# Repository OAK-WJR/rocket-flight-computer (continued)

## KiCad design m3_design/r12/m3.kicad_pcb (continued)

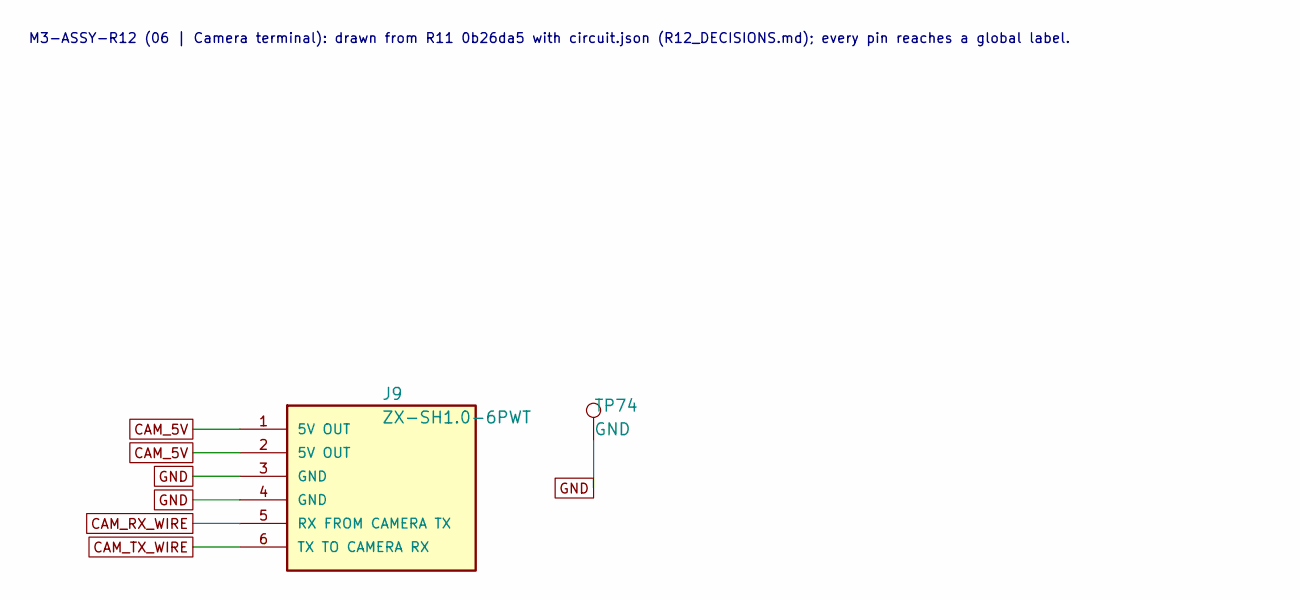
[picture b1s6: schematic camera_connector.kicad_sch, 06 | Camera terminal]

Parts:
J9: ZX-SH1.0-6PWT; M3_SHC_6P; Manufacturer Part ZX-SH1.0-6PWT; LCSC C7430448
TP74: GND; M3_TestPad_1.5

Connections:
CAM_5V: J9.1 (5V OUT), J9.2 (5V OUT); also elsewhere on the board
CAM_RX_WIRE: J9.5 (RX FROM CAMERA TX); also elsewhere on the board
CAM_TX_WIRE: J9.6 (TX TO CAMERA RX); also elsewhere on the board
GND: J9.3 (GND), J9.4 (GND), TP74.1; also elsewhere on the board

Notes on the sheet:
M3-ASSY-R12 (06 | Camera terminal): drawn from R11 0b26da5 with circuit.json (R12_DECISIONS.md); every pin reaches a global label.

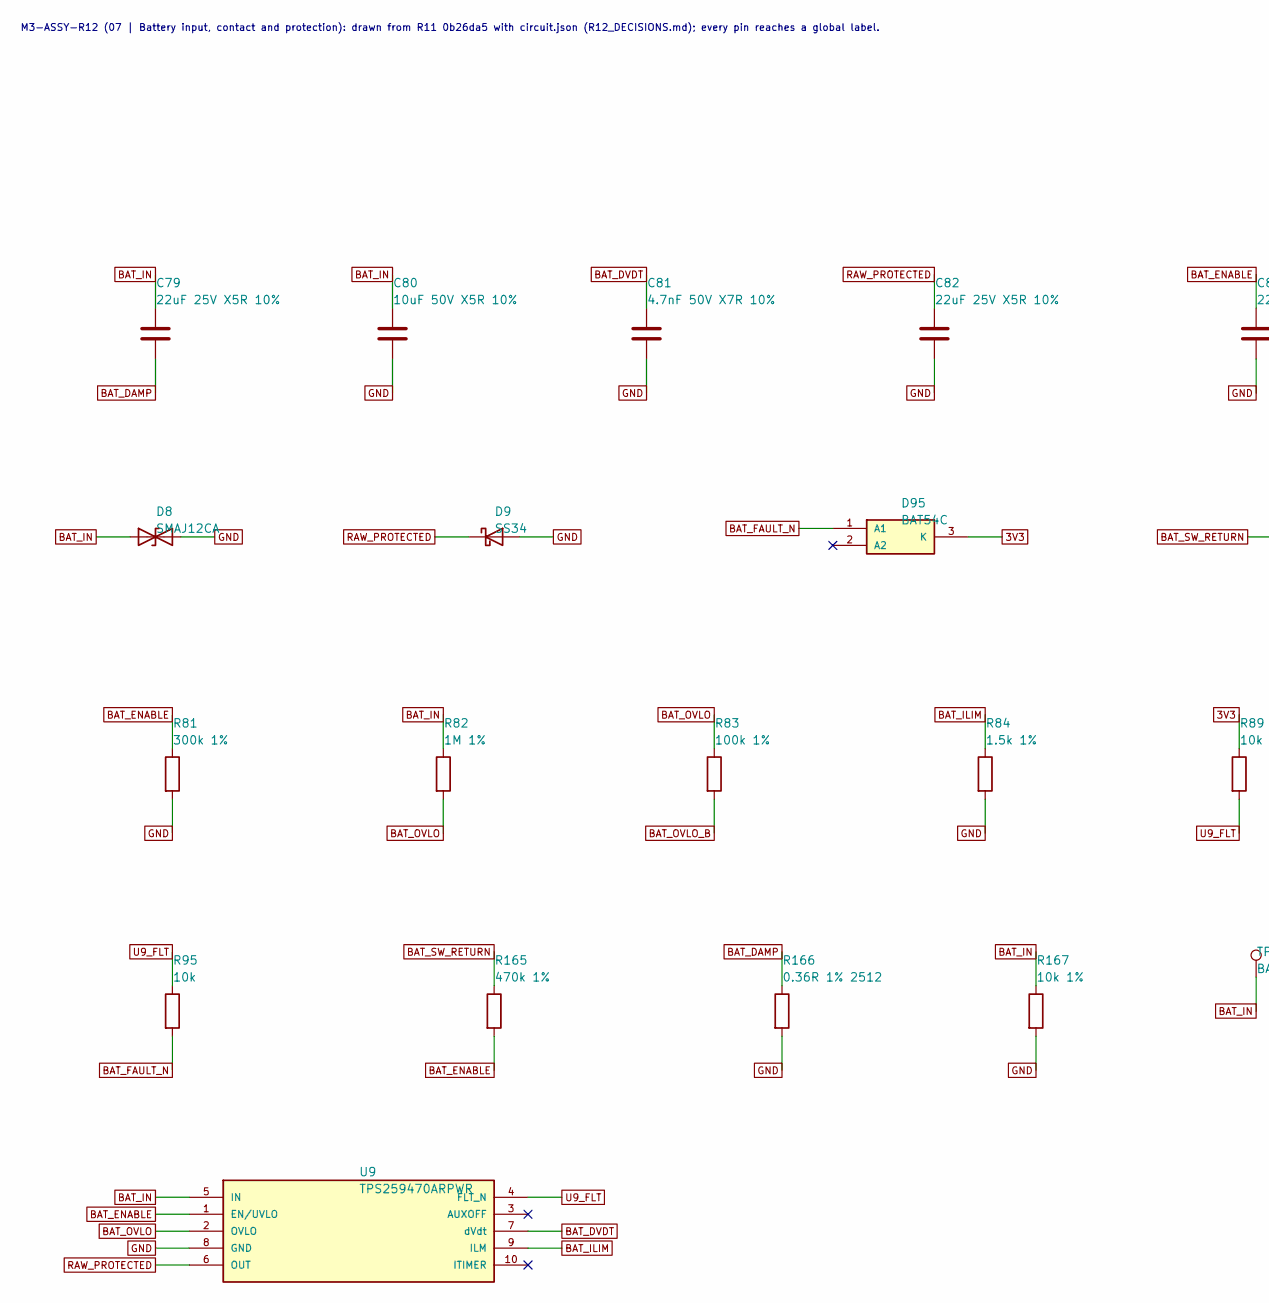
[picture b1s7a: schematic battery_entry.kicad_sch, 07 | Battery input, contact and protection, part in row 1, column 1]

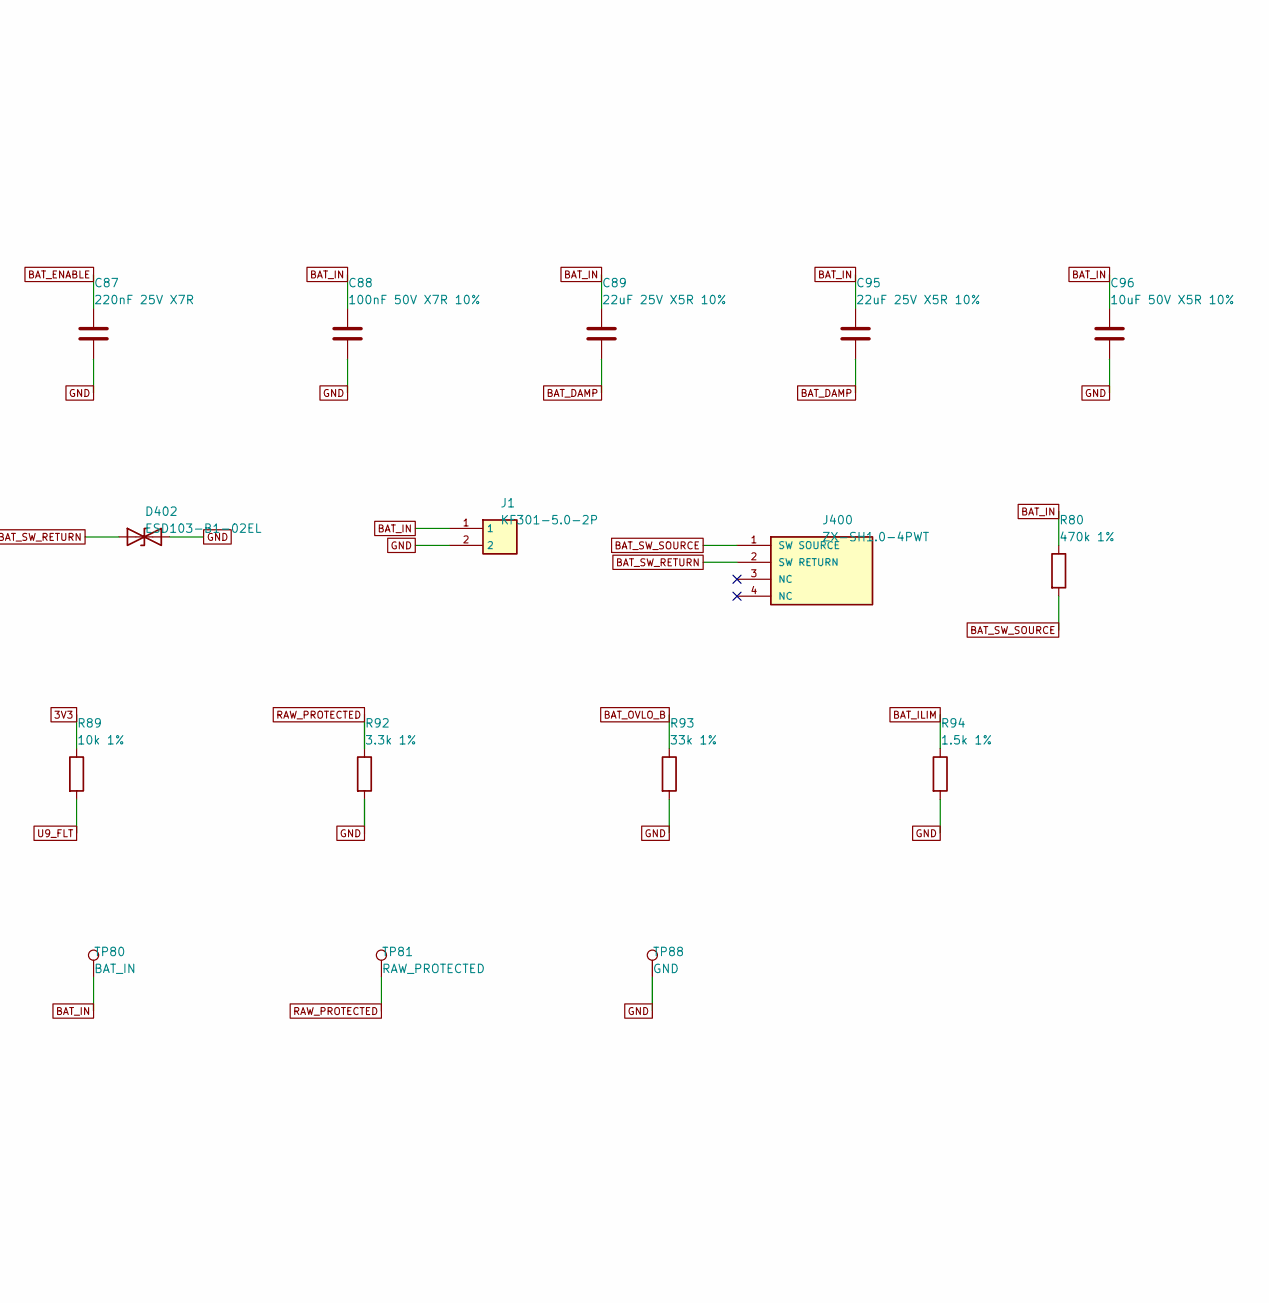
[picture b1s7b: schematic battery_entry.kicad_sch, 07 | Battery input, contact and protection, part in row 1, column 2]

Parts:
C79, C82, C89, C95: 22uF 25V X5R 10%; C_1206_3216Metric; Manufacturer Part CL31A226KAHNNNE; LCSC C12891
C80, C96: 10uF 50V X5R 10%; C_1206_3216Metric; Manufacturer Part CL31A106KBHNNNE; LCSC C13585
C81: 4.7nF 50V X7R 10%; C0402; Manufacturer Part 0402B472K500NT; LCSC C1538
C87: 220nF 25V X7R; C0603; Manufacturer Part CL10B224KA8NNNC; LCSC C21120
C88: 100nF 50V X7R 10%; C0402; Manufacturer Part CL05B104KB54PNC; LCSC C307331
D8: SMAJ12CA; D_SMA; Manufacturer Part SMAJ12CA; LCSC C19077532
D9: SS34; D_SMA; Manufacturer Part SS34; LCSC C8678
D95: BAT54C; SOT-23-3_L2.9-W1.3-P1.90-LS2.4-BR; Manufacturer Part BAT54C,215; LCSC C37704
D402: ESD103-B1-02EL; M3_TSLP_2_20; Manufacturer Part ESD103-B1-02EL E6327; LCSC C535146
J1: KF301-5.0-2P; M3_KF301_5P0_2P_BU; Manufacturer Part KF301-5.0-2P; LCSC C474881
J400: ZX-SH1.0-4PWT; M3_SHC_4P; Manufacturer Part ZX-SH1.0-4PWT; LCSC C7430446
R80, R165: 470k 1%; R_0603_1608Metric; Manufacturer Part 0603WAF4703T5E; LCSC C23178
R81: 300k 1%; R_0603_1608Metric; Manufacturer Part 0603WAF3003T5E; LCSC C23024
R82: 1M 1%; R0402; Manufacturer Part 0402WGF1004TCE; LCSC C26083
R83: 100k 1%; R0402; Manufacturer Part 0402WGF1003TCE; LCSC C25741
R84, R94: 1.5k 1%; R0402; Manufacturer Part 0402WGF1501TCE; LCSC C25867
R89, R167: 10k 1%; R0402; Manufacturer Part 0402WGF1002TCE; LCSC C25744
R92: 3.3k 1%; R_0603_1608Metric; Manufacturer Part 0603WAF3301T5E; LCSC C22978
R93: 33k 1%; R0402; Manufacturer Part 0402WGF3302TCE; LCSC C25779
R95: 10k; R0402; Manufacturer Part 0402WGF1002TCE; LCSC C25744
R166: 0.36R 1% 2512; M3_R2512_UR; Manufacturer Part 25121WF360LT4E; LCSC C168925
TP80: BAT_IN; M3_TestPad_1.5
TP81: RAW_PROTECTED; M3_TestPad_1.5
TP88: GND; M3_TestPad_1.5
U9: TPS259470ARPWR; M3_TPS25947_RPW; Manufacturer Part TPS259470ARPWR; LCSC C3662799

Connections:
3V3: D95.3 (K), R89.1; also elsewhere on the board
BAT_DAMP: C79.2, C89.2, C95.2, R166.1
BAT_DVDT: C81.1, U9.7 (dVdt)
BAT_ENABLE: C87.1, R81.1, R165.2, U9.1 (EN/UVLO)
BAT_FAULT_N: D95.1 (A1), R95.2; also elsewhere on the board
BAT_ILIM: R84.1, R94.1, U9.9 (ILM)
BAT_IN: C79.1, C80.1, C88.1, C89.1, C95.1, C96.1, D8.1 (A1), J1.1, R80.1, R82.1, R167.1, TP80.1, U9.5 (IN); also elsewhere on the board
BAT_OVLO: R82.2, R83.1, U9.2 (OVLO)
BAT_OVLO_B: R83.2, R93.1
BAT_SW_RETURN: D402.1 (A1), J400.2 (SW RETURN), R165.1
BAT_SW_SOURCE: J400.1 (SW SOURCE), R80.2
GND: C80.2, C81.2, C82.2, C87.2, C88.2, C96.2, D8.2 (A2), D9.2 (A), D402.2 (A2), J1.2, R81.2, R84.2, R92.2, R93.2, R94.2, R166.2, R167.2, TP88.1, U9.8 (GND); also elsewhere on the board
RAW_PROTECTED: C82.1, D9.1 (K), R92.1, TP81.1, U9.6 (OUT); also elsewhere on the board
U9_FLT: R89.2, R95.1, U9.4 (FLT_N)

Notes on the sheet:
M3-ASSY-R12 (07 | Battery input, contact and protection): drawn from R11 0b26da5 with circuit.json (R12_DECISIONS.md); every pin reaches a global label.

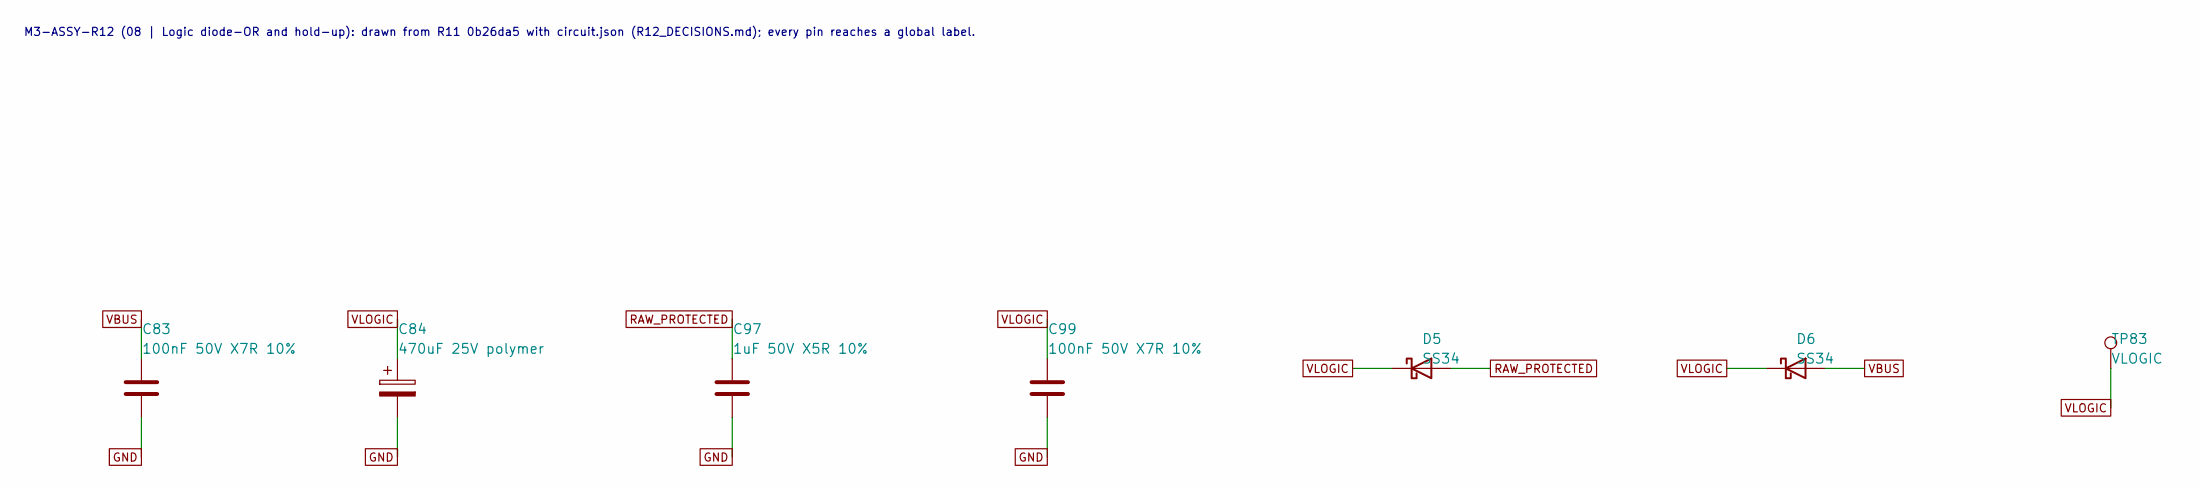
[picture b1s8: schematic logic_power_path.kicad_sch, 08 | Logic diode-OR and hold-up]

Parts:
C83, C99: 100nF 50V X7R 10%; C0402; Manufacturer Part CL05B104KB54PNC; LCSC C307331
C84: 470uF 25V polymer; M3_CAP_D8_SMD; Manufacturer Part HV1E477M0810PZ; LCSC C5246546
C97: 1uF 50V X5R 10%; C0603; Manufacturer Part CL10A105KB8NNNC; LCSC C15849
D5, D6: SS34; D_SMA; Manufacturer Part SS34; LCSC C8678
TP83: VLOGIC; M3_TestPad_1.5

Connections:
GND: C83.2, C84.2, C97.2, C99.2; also elsewhere on the board
RAW_PROTECTED: C97.1, D5.2 (A); also elsewhere on the board
VBUS: C83.1, D6.2 (A); also elsewhere on the board
VLOGIC: C84.1, C99.1, D5.1 (K), D6.1 (K), TP83.1; also elsewhere on the board

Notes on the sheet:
M3-ASSY-R12 (08 | Logic diode-OR and hold-up): drawn from R11 0b26da5 with circuit.json (R12_DECISIONS.md); every pin reaches a global label.

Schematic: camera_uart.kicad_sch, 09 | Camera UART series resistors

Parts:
R100, R101: 1k 1%; R0402; Manufacturer Part 0402WGF1001TCE; LCSC C11702

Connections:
CAM_MCU_RX: R100.2; also elsewhere on the board
CAM_MCU_TX: R101.1; also elsewhere on the board
CAM_RX_WIRE: R100.1; also elsewhere on the board
CAM_TX_WIRE: R101.2; also elsewhere on the board

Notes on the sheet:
M3-ASSY-R12 (09 | Camera UART series resistors): drawn from R11 0b26da5 with circuit.json (R12_DECISIONS.md); every pin reaches a global label.

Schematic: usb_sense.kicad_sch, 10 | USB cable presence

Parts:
R9: 1k; R0402; Manufacturer Part 0402WGF1001TCE; LCSC C11702
R110: 1.5k 1%; R0402; Manufacturer Part 0402WGF1501TCE; LCSC C25867

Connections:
GND: R110.2; also elsewhere on the board
VBUS: R9.1; also elsewhere on the board
VBUS_SENSE: R9.2, R110.1; also elsewhere on the board

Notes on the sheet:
M3-ASSY-R12 (10 | USB cable presence): drawn from R11 0b26da5 with circuit.json (R12_DECISIONS.md); every pin reaches a global label.

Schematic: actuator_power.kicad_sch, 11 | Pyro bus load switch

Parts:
C120: 1uF 50V X5R 10%; C0603; Manufacturer Part CL10A105KB8NNNC; LCSC C15849
C123: 10nF 50V X7R 10%; C0402; Manufacturer Part CL05B103KB5NNNC; LCSC C15195
Q120, Q121: AO3401A; SOT-23-3_L2.9-W1.3-P1.90-LS2.4-BR; Manufacturer Part AO3401A; LCSC C15127
Q122: AO3400A; SOT-23-3_L2.9-W1.3-P1.90-LS2.4-BR; Manufacturer Part AO3400A; LCSC C20917
R118, R121: 10k; R0402; Manufacturer Part 0402WGF1002TCE; LCSC C25744
R119, R120: 100k; R0402; Manufacturer Part 0402WGF1003TCE; LCSC C25741
R122: 1k; R0402; Manufacturer Part 0402WGF1001TCE; LCSC C11702
R123: 2k; R0402; Manufacturer Part 0402WGF2001TCE; LCSC C4109
TP120: RAW_ACT; M3_TestPad_1.5

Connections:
ACT_DRV: Q122.3 (D), R121.2
ACT_EN: C123.1, Q122.1 (G), R118.1, R122.2, R123.1
ACT_EN_MCU: R122.1; also elsewhere on the board
ACT_FET_S: C120.1, Q120.2 (S), Q121.2 (S), R119.2, R120.1
ACT_GATE: C120.2, Q120.1 (G), Q121.1 (G), R119.1, R120.2, R121.1
BAT_IN: Q120.3 (D); also elsewhere on the board
GND: C123.2, Q122.2 (S), R118.2, R123.2; also elsewhere on the board
RAW_ACT: Q121.3 (D), TP120.1; also elsewhere on the board

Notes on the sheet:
M3-ASSY-R12 (11 | Pyro bus load switch): drawn from R11 0b26da5 with circuit.json (R12_DECISIONS.md); every pin reaches a global label.

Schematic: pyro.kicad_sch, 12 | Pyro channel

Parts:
C126: 220nF 25V X7R; C0603; Manufacturer Part CL10B224KA8NNNC; LCSC C21120
C127, C129: 10nF 50V X7R 10%; C0402; Manufacturer Part CL05B103KB5NNNC; LCSC C15195
C128: 100nF 50V X7R 10%; C0402; Manufacturer Part CL05B104KB54PNC; LCSC C307331
D120: BAT54C; SOT-23-3_L2.9-W1.3-P1.90-LS2.4-BR; Manufacturer Part BAT54C,215; LCSC C37704
J121: DB125-3.5-2P-BK-S; M3_DB125_2P_BK; Manufacturer Part DB125-3.5-2P-BK-S; LCSC C52993880
Q124: AO3400A; SOT-23-3_L2.9-W1.3-P1.90-LS2.4-BR; Manufacturer Part AO3400A; LCSC C20917
R126: 220R; R0402; Manufacturer Part 0402WGF2200TCE; LCSC C25091
R127: 1k; R0402; Manufacturer Part 0402WGF1001TCE; LCSC C11702
R128: 10k; R0402; Manufacturer Part 0402WGF1002TCE; LCSC C25744
R129, R131, R132, R136, R173, R175: 5.1k; R0402; Manufacturer Part 0402WGF5101TCE; LCSC C25905
R130, R133, R178, R180: 2k; R0402; Manufacturer Part 0402WGF2001TCE; LCSC C4109
R134: 2R 1% 2W pulse; R2512; Manufacturer Part CRM2512-FX-2R00ELF; LCSC C3013496
TP122: PYRO1_GATE; M3_TestPad_1.5

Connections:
3V3: R136.1; also elsewhere on the board
ARM1_SENSE: C129.1, R133.1, R175.2, R180.1; also elsewhere on the board
ARM1_SENSE_MID: R132.2, R175.1
GND: C126.2, C127.2, C128.2, C129.2, Q124.2 (S), R127.2, R128.2, R130.2, R133.2, R178.2, R180.2; also elsewhere on the board
PYRO1_COLD: D120.3 (K), R131.2
PYRO1_COLD_PU: D120.1 (A1), R136.2
PYRO1_CONT: C127.1, R129.2, R130.1, R178.1; also elsewhere on the board
PYRO1_CONT_MID: R129.1, R173.2
PYRO1_GATE: C126.1, Q124.1 (G), R126.2, R128.1, TP122.1
PYRO1_GATE_N: R126.1, R127.1; also elsewhere on the board
PYRO1_IGN: J121.2, R134.1
PYRO1_OUT: C128.1, J121.1, Q124.3 (D), R131.1, R173.1
RAW_ACT: R132.1, R134.2; also elsewhere on the board

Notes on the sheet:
M3-ASSY-R12 (12 | Pyro channel): drawn from R11 0b26da5 with circuit.json (R12_DECISIONS.md); every pin reaches a global label.

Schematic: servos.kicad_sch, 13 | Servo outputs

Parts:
D121: SRV05-4; SOT-23-6_L2.9-W1.6-P0.95-LS2.8-BL; Manufacturer Part SRV05-4-P-T7; LCSC C85364
J122: ZX-SH1.0-6PWT; M3_SHC_6P; Manufacturer Part ZX-SH1.0-6PWT; LCSC C7430448
R150, R151, R152, R153: 1k 0603; R_0603_1608Metric; Manufacturer Part 0603WAF1001T5E; LCSC C21190
R154, R155, R156, R157: 10k; R0402; Manufacturer Part 0402WGF1002TCE; LCSC C25744

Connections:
3V3: D121.5 (VCC); also elsewhere on the board
GND: D121.2 (GND), J122.5 (GND), R154.2, R155.2, R156.2, R157.2; also elsewhere on the board
SERVO1_MCU: D121.1 (IO1), R150.1, R154.1; also elsewhere on the board
SERVO1_OUT: J122.1 (SERVO1), R150.2
SERVO2_MCU: D121.3 (IO2), R151.1, R155.1; also elsewhere on the board
SERVO2_OUT: J122.2 (SERVO2), R151.2
SERVO3_MCU: D121.4 (IO3), R152.1, R156.1; also elsewhere on the board
SERVO3_OUT: J122.3 (SERVO3), R152.2
SERVO4_MCU: D121.6 (IO4), R153.1, R157.1; also elsewhere on the board
SERVO4_OUT: J122.4 (SERVO4), R153.2

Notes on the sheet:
M3-ASSY-R12 (13 | Servo outputs): drawn from R11 0b26da5 with circuit.json (R12_DECISIONS.md); every pin reaches a global label.

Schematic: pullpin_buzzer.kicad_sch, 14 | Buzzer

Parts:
D123: 1N5819WS; SOD-323_L1.8-W1.3-LS2.5-RD; Manufacturer Part 1N5819WS; LCSC C191023
LS120: QMB-09B-03; M3_BUZ_TH_D9_P4; Manufacturer Part QMB-09B-03; LCSC C96256
Q123: AO3400A; SOT-23-3_L2.9-W1.3-P1.90-LS2.4-BR; Manufacturer Part AO3400A; LCSC C20917
R162: 1k; R0402; Manufacturer Part 0402WGF1001TCE; LCSC C11702
R163: 10k; R0402; Manufacturer Part 0402WGF1002TCE; LCSC C25744

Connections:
3V3: D123.1 (K), LS120.1 (+); also elsewhere on the board
BUZZ_DRV: R162.1; also elsewhere on the board
BUZZ_G: Q123.1 (G), R162.2, R163.1
BUZZ_OUT: D123.2 (A), LS120.2 (-), Q123.3 (D)
GND: Q123.2 (S), R163.2; also elsewhere on the board

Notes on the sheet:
M3-ASSY-R12 (14 | Buzzer): drawn from R11 0b26da5 with circuit.json (R12_DECISIONS.md); every pin reaches a global label.

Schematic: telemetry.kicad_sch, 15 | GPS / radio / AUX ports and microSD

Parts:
C460: 100nF 50V X7R 10%; C0402; Manufacturer Part CL05B104KB54PNC; LCSC C307331
C461: 22uF 25V X5R 10%; C_1206_3216Metric; Manufacturer Part CL31A226KAHNNNE; LCSC C12891
J410: ZX-SH1.0-6PWT; M3_SHC_6P; Manufacturer Part ZX-SH1.0-6PWT; LCSC C7430448
J420, J440: ZX-SH1.0-4PWT; M3_SHC_4P; Manufacturer Part ZX-SH1.0-4PWT; LCSC C7430446
J430: 104031-0811; M3_MICROSD_MOLEX_104031; Manufacturer Part 1040310811; LCSC C585350
R440, R441, R450, R451, R470, R471: 1k 1%; R0402; Manufacturer Part 0402WGF1001TCE; LCSC C11702
R460, R461, R462, R463, R464: 10k 1%; R0402; Manufacturer Part 0402WGF1002TCE; LCSC C25744

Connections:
3V3: C460.1, C461.1, J430.4 (VDD), R460.2, R461.2, R462.2, R463.2, R464.2; also elsewhere on the board
AUX_RX_MCU: R470.2; also elsewhere on the board
AUX_RX_WIRE: J440.4 (RXI), R470.1
AUX_TX_MCU: R471.1; also elsewhere on the board
AUX_TX_WIRE: J440.3 (TXO), R471.2
GND: C460.2, C461.2, J410.1 (GND), J420.1 (GND), J430.6 (VSS), J430.9 (G2), J430.10 (G1), J430.13 (G4), J430.14 (G3), J440.1 (GND); also elsewhere on the board
GPS_RX_MCU: R440.2; also elsewhere on the board
GPS_RX_WIRE: J410.4 (RXI), R440.1
GPS_TX_MCU: R441.1; also elsewhere on the board
GPS_TX_WIRE: J410.3 (TXO), R441.2
PORT_4V8: J410.2 (4V8), J420.2 (4V8), J440.2 (4V8); also elsewhere on the board
RADIO_RX_MCU: R450.2; also elsewhere on the board
RADIO_RX_WIRE: J420.4 (RXI), R450.1
RADIO_TX_MCU: R451.1; also elsewhere on the board
RADIO_TX_WIRE: J420.3 (TXO), R451.2
SD_CS: J430.2 (CD_DAT3_CS), R460.1; also elsewhere on the board
SD_DAT1: J430.8 (DAT1), R463.1
SD_DAT2: J430.1 (DAT2), R464.1
SD_MISO: J430.7 (DAT0_DO), R462.1; also elsewhere on the board
SD_MOSI: J430.3 (CMD_DI), R461.1; also elsewhere on the board
SD_SCK: J430.5 (CLK); also elsewhere on the board

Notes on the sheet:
M3-ASSY-R12 (15 | GPS / radio / AUX ports and microSD): drawn from R11 0b26da5 with circuit.json (R12_DECISIONS.md); every pin reaches a global label.

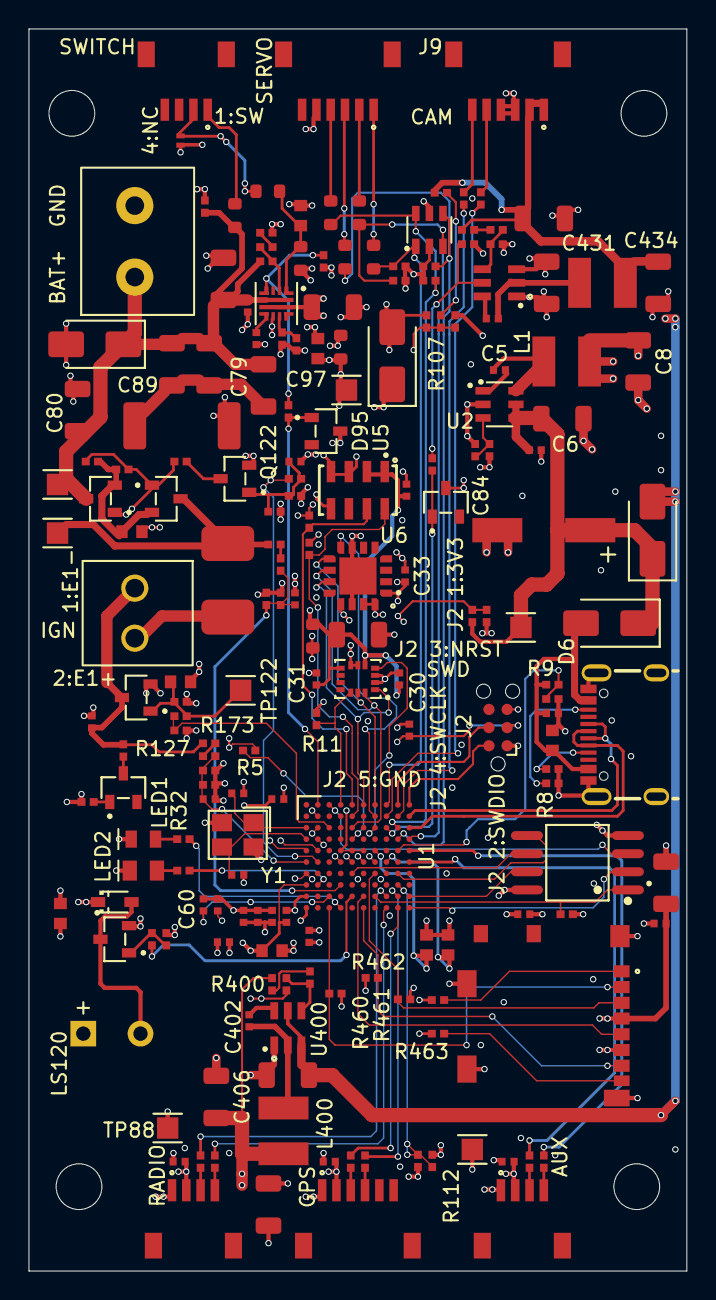
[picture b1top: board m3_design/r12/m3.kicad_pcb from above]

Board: 4 copper layers, 46.0 x 86.8 mm, 193 parts (0 on the bottom side), 116 nets.

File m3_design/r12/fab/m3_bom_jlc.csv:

Comment,Designator,Footprint,LCSC Part #,Manufacturer Part,Qty,Assembly
100nF 50V X7R 10%,"C5,C13,C14,C15,C16,C17,C18,C21,C24,C29,C30,C31,C32,C33,C83,C88,C99,C128,C402,C410,C420,C432,C444,C460",C0402,C307331,CL05B104KB54PNC,24,SMT
22uF 25V X5R 10%,"C6,C8,C10,C79,C82,C89,C95,C400,C406,C407,C431,C433,C434,C461",C_1206_3216Metric,C12891,CL31A226KAHNNNE,14,SMT
2.2uF 16V X5R 10%,"C19,C20",C0603,C23630,CL10A225KO8NNNC,2,SMT
1uF 50V X5R 10%,"C22,C97,C120",C0603,C15849,CL10A105KB8NNNC,3,SMT
4.7uF 16V X5R 10%,"C23,C28",C0603,C19666,CL10A475KO8NNNC,2,SMT
15pF 50V C0G 5%,"C25,C26",C0402,C1548,0402CG150J500NT,2,SMT
10nF 50V X7R 10%,"C60,C94,C123,C127,C129",C0402,C15195,CL05B103KB5NNNC,5,SMT
10uF 50V X5R 10%,"C80,C96",C_1206_3216Metric,C13585,CL31A106KBHNNNE,2,SMT
4.7nF 50V X7R 10%,C81,C0402,C1538,0402B472K500NT,1,SMT
470uF 25V polymer,C84,M3_CAP_D8_SMD,C5246546,HV1E477M0810PZ,1,SMT
220nF 25V X7R,"C87,C126",C0603,C21120,CL10B224KA8NNNC,2,SMT
SS34,"D5,D6,D9",D_SMA,C8678,SS34,3,SMT
SMAJ12CA,D8,D_SMA,C19077532,SMAJ12CA,1,SMT
BAT54C,"D95,D120,D436",SOT-23-3_L2.9-W1.3-P1.90-LS2.4-BR,C37704,"BAT54C,215",3,SMT
SRV05-4,D121,SOT-23-6_L2.9-W1.6-P0.95-LS2.8-BL,C85364,SRV05-4-P-T7,1,SMT
1N5819WS,D123,SOD-323_L1.8-W1.3-LS2.5-RD,C191023,1N5819WS,1,SMT
ESD103-B1-02EL,D402,M3_TSLP_2_20,C535146,ESD103-B1-02EL E6327,1,SMT
KF301-5.0-2P,J1,M3_KF301_5P0_2P_BU,C474881,KF301-5.0-2P,1,THT (JLC THT assembly)
USB-C 2.0,J3,USB-C_SMD-TYPE-C-31-M-12_1,C165948,TYPE-C-31-M-12,1,SMT
ZX-SH1.0-6PWT,"J9,J122,J410",M3_SHC_6P,C7430448,ZX-SH1.0-6PWT,3,SMT
DB125-3.5-2P-BK-S,J121,M3_DB125_2P_BK,C52993880,DB125-3.5-2P-BK-S,1,THT (JLC THT assembly)
ZX-SH1.0-4PWT,"J400,J420,J440",M3_SHC_4P,C7430446,ZX-SH1.0-4PWT,3,SMT
104031-0811,J430,M3_MICROSD_MOLEX_104031,C585350,1040310811,1,SMT
4.7uH,"L1,L400,L401",IND-SMD_L4.0-W4.0,C57269,SWPA4030S4R7MT,3,SMT
RED,LED1,M3_NCD0805R1_K1,C84256,NCD0805R1,1,SMT
YEL,LED2,M3_KT0805Y_A1,C2296,KT-0805Y,1,SMT
QMB-09B-03,LS120,M3_BUZ_TH_D9_P4,C96256,QMB-09B-03,1,THT (JLC THT assembly)
AO3401A,"Q120,Q121",SOT-23-3_L2.9-W1.3-P1.90-LS2.4-BR,C15127,AO3401A,2,SMT
AO3400A,"Q122,Q123,Q124",SOT-23-3_L2.9-W1.3-P1.90-LS2.4-BR,C20917,AO3400A,3,SMT
10k; 10k 1%,"R5,R10,R11,R89,R95,R118,R121,R128,R154,R155,R156,R157,R163,R167,R434,R435,R460,R461,R462,R463,R464",R0402,C25744,0402WGF1002TCE,21,SMT
5.1k,"R7,R8,R104,R107,R129,R131,R132,R136,R173,R175,R404,R436",R0402,C25905,0402WGF5101TCE,12,SMT
1k; 1k 1%,"R9,R100,R101,R122,R127,R162,R440,R441,R450,R451,R470,R471",R0402,C11702,0402WGF1001TCE,12,SMT
4.7k,"R12,R13",R0402,C25900,0402WGF4701TCE,2,SMT
47k 1%,"R14,R111,R400,R431",R0402,C25792,0402WGF4702TCE,4,SMT
20k 1%,R15,R0402,C25765,0402WGF2002TCE,1,SMT
220R,"R32,R33,R126",R0402,C25091,0402WGF2200TCE,3,SMT
100k 0.1%,R60,R0402,C852472,RT0402BRD07100KL,1,SMT
10k 0.1%,"R61,R401",R0402,C190095,RT0402BRD0710KL,2,SMT
470k 1%,"R80,R165",R_0603_1608Metric,C23178,0603WAF4703T5E,2,SMT
300k 1%,R81,R_0603_1608Metric,C23024,0603WAF3003T5E,1,SMT
1M 1%,R82,R0402,C26083,0402WGF1004TCE,1,SMT
100k 1%; 100k,"R83,R112,R119,R120",R0402,C25741,0402WGF1003TCE,4,SMT
1.5k 1%,"R84,R94,R110",R0402,C25867,0402WGF1501TCE,3,SMT
3.3k 1%,R92,R_0603_1608Metric,C22978,0603WAF3301T5E,1,SMT
33k 1%,R93,R0402,C25779,0402WGF3302TCE,1,SMT
2k,"R105,R106,R123,R130,R133,R178,R180",R0402,C4109,0402WGF2001TCE,7,SMT
2R 1% 2W pulse,R134,R2512,C3013496,CRM2512-FX-2R00ELF,1,SMT
1k 0603,"R150,R151,R152,R153",R_0603_1608Metric,C21190,0603WAF1001T5E,4,SMT
2.2R 1%,R164,R_0603_1608Metric,C22939,0603WAF220KT5E,1,SMT
0.36R 1% 2512,R166,M3_R2512_UR,C168925,25121WF360LT4E,1,SMT
51k 1%,R433,R0402,C25794,0402WGF5102TCE,1,SMT
STM32H743VIH6,U1,M3_TFBGA100_8x8_P0.8,C964146,STM32H743VIH6,1,SMT
LMR50410XDBVR,U2,SOT-23-6_L2.9-W1.6-P0.95-LS2.8-BL,C2841056,LMR50410XDBVR,1,SMT
W25Q128JVSIQ,U3,SOIC-8_L5.3-W5.3-P1.27-LS8.0-BL,C97521,W25Q128JVSIQ,1,SMT
LSM6DSVETR,U4,LGA-14_L3.0-W2.5-P0.50-TL,C41785564,LSM6DSVETR,1,SMT
MS5607-02BA03,U5,SENSORS-SMD_MS5611-01BA03,C97627,MS560702BA03-50,1,SMT
FXLS90322AESR2,U6,M3_FXLS_HLQFN16,C5190712,FXLS90322AESR2,1,SMT
TPS259470ARPWR,U9,M3_TPS25947_RPW,C3662799,TPS259470ARPWR,1,SMT
TPS563208DDCR,"U400,U403",M3_TSOT23_6_DDC,C468250,TPS563208DDCR,2,SMT
25MHz CL12pF,Y1,CRYSTAL-SMD_4P-L3.2-W2.5-BL,C9006,X322525MOB4SI,1,SMT

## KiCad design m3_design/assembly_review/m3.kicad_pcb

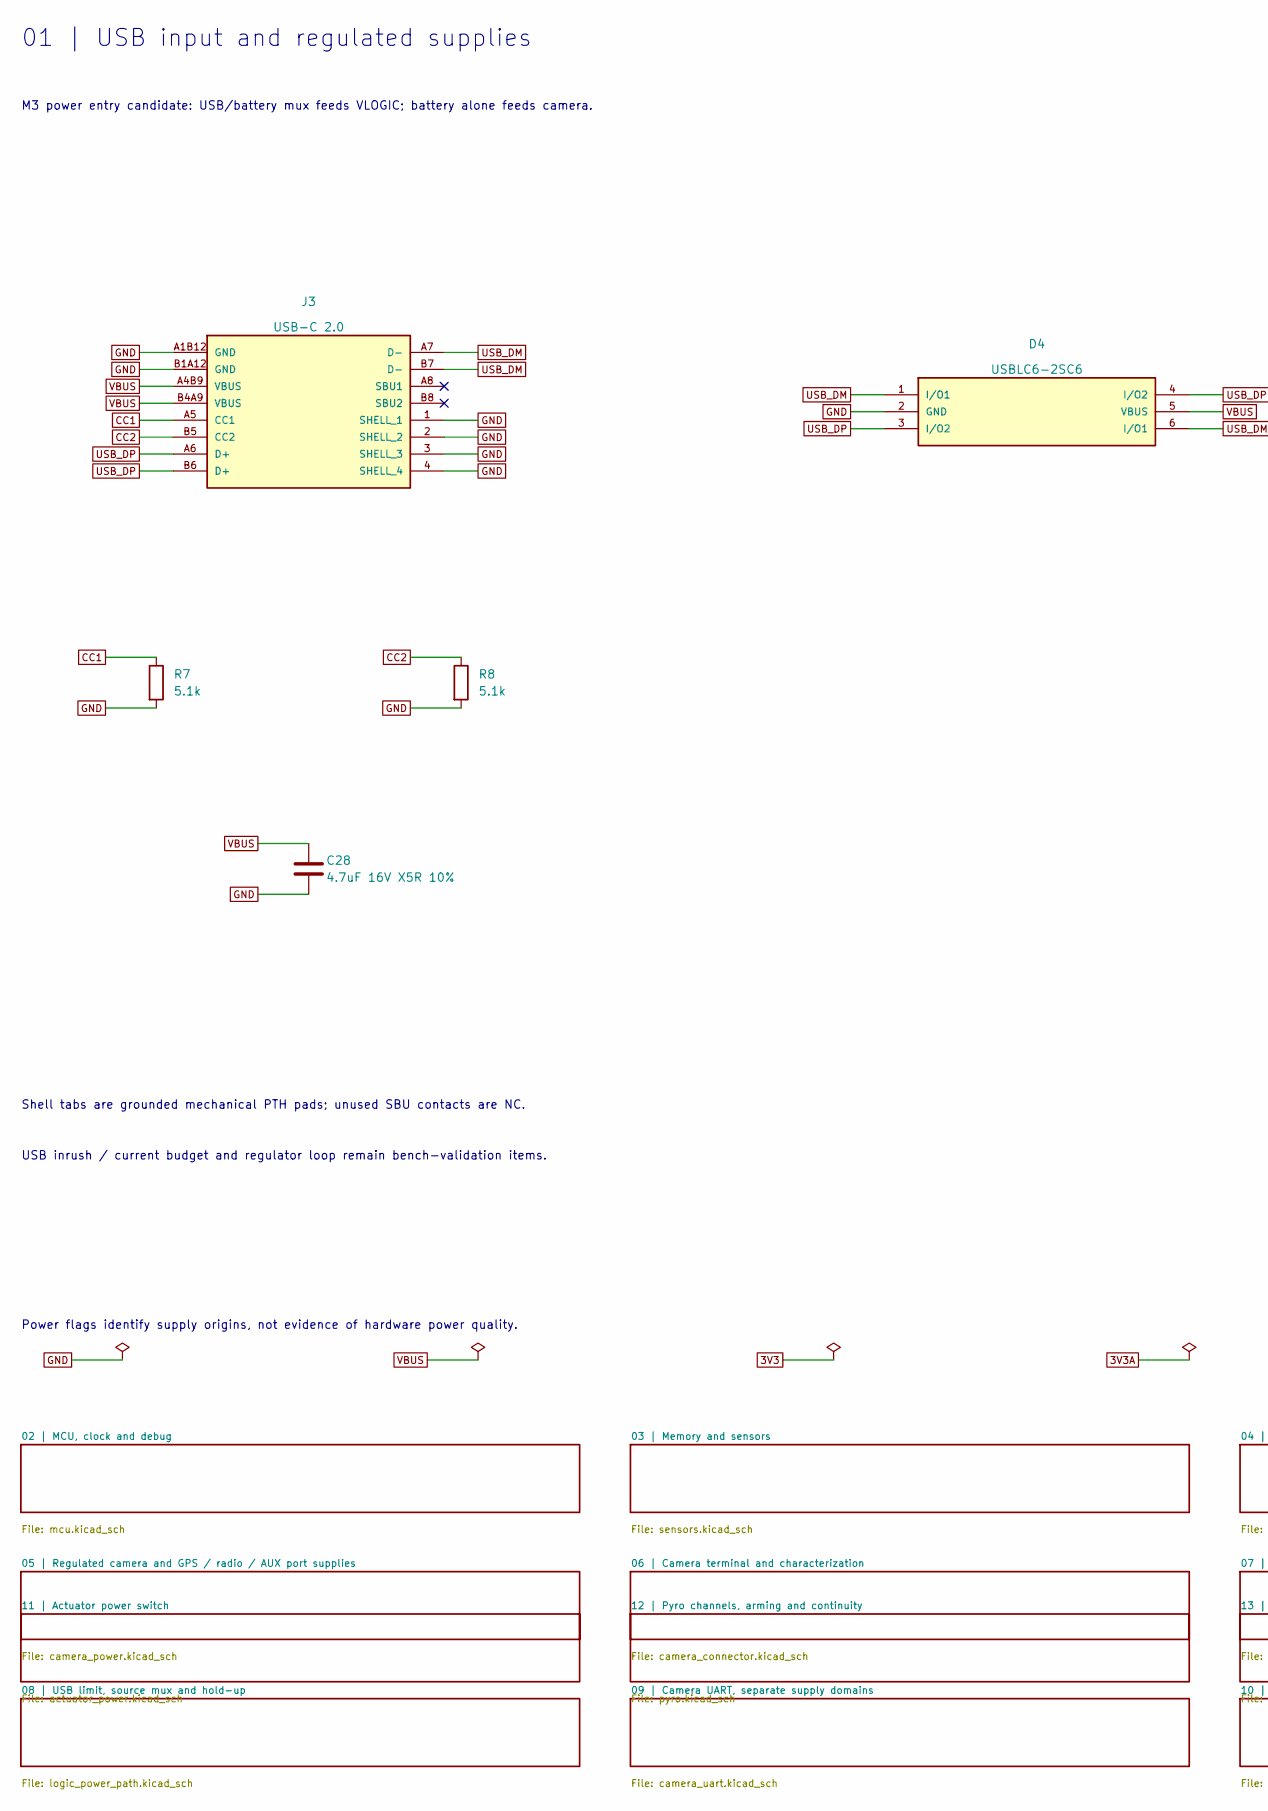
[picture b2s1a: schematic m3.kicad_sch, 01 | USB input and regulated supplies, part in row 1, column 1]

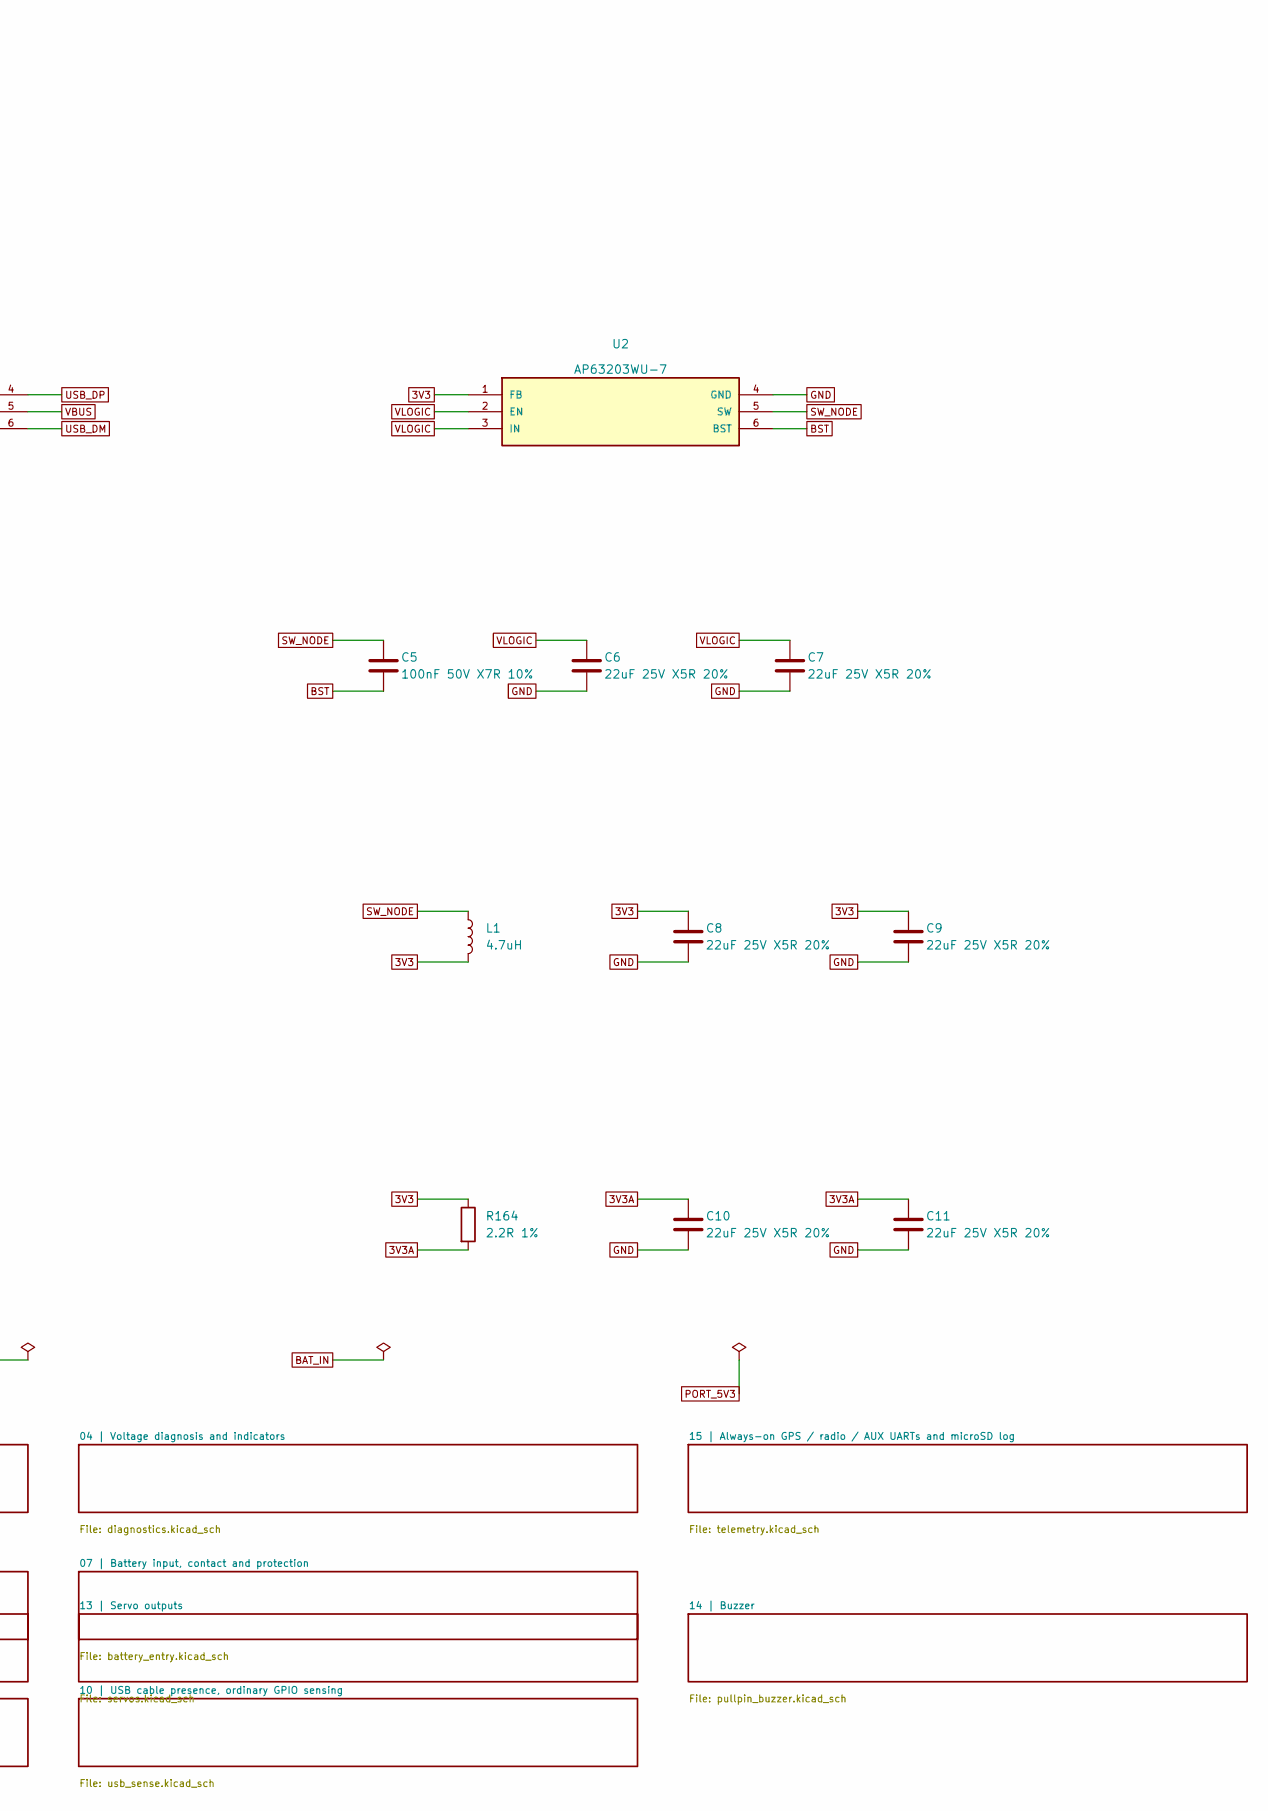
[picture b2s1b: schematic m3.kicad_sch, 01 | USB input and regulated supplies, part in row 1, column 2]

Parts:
C5: 100nF 50V X7R 10%; C0402; Manufacturer Part CL05B104KB54PNC; LCSC C307331
C6, C7, C8, C9, C10, C11: 22uF 25V X5R 20%; C0805; Manufacturer Part CL21A226MAQNNNE; LCSC C45783
C28: 4.7uF 16V X5R 10%; C0603; Manufacturer Part CL10A475KO8NNNC; LCSC C19666
D4: USBLC6-2SC6; SOT-23-6_L2.9-W1.6-P0.95-LS2.8-BL; Manufacturer Part USBLC6-2SC6; LCSC C7519
J3: USB-C 2.0; USB-C_SMD-TYPE-C-31-M-12_1; Manufacturer Part TYPE-C-31-M-12; LCSC C165948
L1: 4.7uH; IND-SMD_L4.0-W4.0; Manufacturer Part SWPA4030S4R7MT; LCSC C57269
R7, R8: 5.1k; R0402; Manufacturer Part 0402WGF5101TCE; LCSC C25905
R164: 2.2R 1%; R_0603_1608Metric; Manufacturer Part 0603WAF220KT5E; LCSC C22939
U2: AP63203WU-7; TSOT-26_L2.9-W1.6-P0.95-LS2.8-BL; Manufacturer Part AP63203WU-7; LCSC C780769

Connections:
3V3: C8.1, C9.1, L1.2, R164.1, U2.1 (FB); also elsewhere on the board
3V3A: C10.1, C11.1, R164.2; also elsewhere on the board
BST: C5.2, U2.6 (BST)
CC1: J3.A5 (CC1), R7.1
CC2: J3.B5 (CC2), R8.1
GND: C6.2, C7.2, C8.2, C9.2, C10.2, C11.2, C28.2, D4.2 (GND), J3.1 (SHELL_1), J3.2 (SHELL_2), J3.3 (SHELL_3), J3.4 (SHELL_4), J3.A1B12 (GND), J3.B1A12 (GND), R7.2, R8.2, U2.4 (GND); also elsewhere on the board
SW_NODE: C5.1, L1.1, U2.5 (SW)
USB_DM: D4.1 (I/O1), D4.6 (I/O1), J3.A7 (D-), J3.B7 (D-); also elsewhere on the board
USB_DP: D4.3 (I/O2), D4.4 (I/O2), J3.A6 (D+), J3.B6 (D+); also elsewhere on the board
VBUS: C28.1, D4.5 (VBUS), J3.A4B9 (VBUS), J3.B4A9 (VBUS); also elsewhere on the board
VLOGIC: C6.1, C7.1, U2.2 (EN), U2.3 (IN); also elsewhere on the board

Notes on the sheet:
01 | USB input and regulated supplies
M3 power entry candidate: USB/battery mux feeds VLOGIC; battery alone feeds camera.
Shell tabs are grounded mechanical PTH pads; unused SBU contacts are NC.
USB inrush / current budget and regulator loop remain bench-validation items.
Power flags identify supply origins, not evidence of hardware power quality.
